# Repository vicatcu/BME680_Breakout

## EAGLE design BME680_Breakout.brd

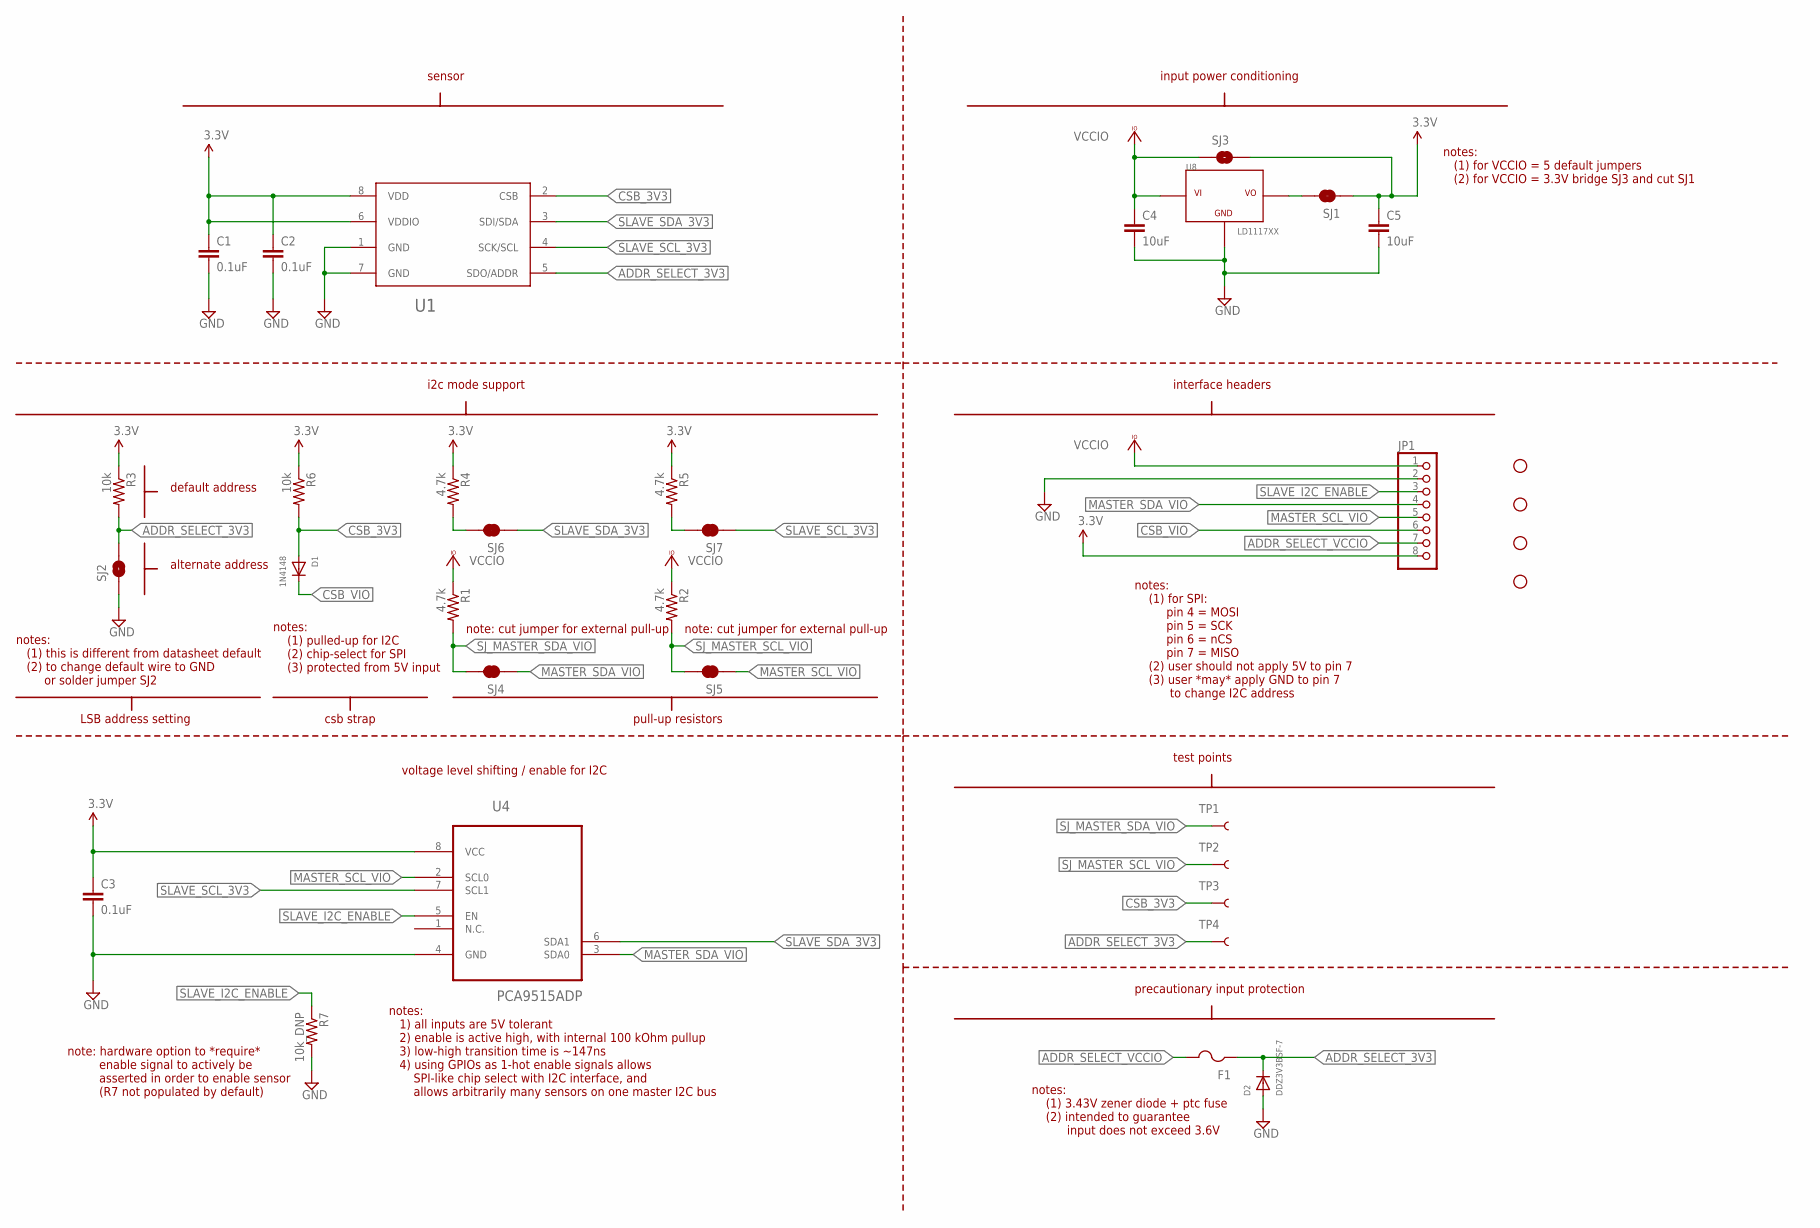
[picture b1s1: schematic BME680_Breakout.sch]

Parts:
C1, C2, C3: 0.1uF; 0805
C4, C5: 10uF; 0805
D1: 1N4148; SOD-323F
D2: DDZ3V3BSF-7; SOD-323F
F1: PTCFUSE-1812; 1812
JP1: PINHD-1X8; 1X08
R1, R2, R4, R5: 4.7k; 0805
R3, R6: 10k; 0805
R7: 10k_DNP; 0805
SJ1, SJ4, SJ5, SJ6, SJ7: JUMPER-PAD-2-NC_BY_TRACE; PAD-JUMPER-2-NC_BY_TRACE_YES_SILK
SJ2: JUMPER-PAD-2-NOYES_SILK; PAD-JUMPER-2-NO_YES_SILK
SJ3: SOLDERJUMPERNC2; SJ_2S-NOTRACE
STANDOFF1, STANDOFF2, STANDOFF3, STANDOFF4: STAND-OFF
TP1, TP2, TP3, TP4: TEST-POINT3X4; PAD.03X.04
U1: BME680
U4: PCA9515ADP; SOT505-1
U8: LD1117XX; DPAK

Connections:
3.3V: C1.1, C2.1, C3.1, C5.1, JP1.8, R3.1, R4.1, R5.1, R6.1, SJ1.1, SJ3.2, U1.6 (VDDIO), U1.8 (VDD), U4.8 (VCC)
ADDR_SELECT_3V3: D2.C, F1.1, R3.2, SJ2.2, TP4.P$1, U1.5 (SDO/ADDR)
ADDR_SELECT_VCCIO: F1.2, JP1.7
CSB_3V3: D1.A, R6.2, TP3.P$1, U1.2 (CSB)
CSB_VIO: D1.C, JP1.6
GND: C1.2, C2.2, C3.2, C4.2, C5.2, D2.A, JP1.2, R7.2, SJ2.1, U1.1 (GND), U1.7 (GND), U4.4 (GND), U8.1 (GND)
MASTER_SCL_VIO: JP1.5, SJ5.1, U4.2 (SCL0)
MASTER_SDA_VIO: JP1.4, SJ4.1, U4.3 (SDA0)
unnamed: SJ1.2, U8.4 (VO)
unnamed: R4.2, SJ6.2
unnamed: R5.2, SJ7.2
SJ_MASTER_SCL_VIO: R2.2, SJ5.2, TP2.P$1
SJ_MASTER_SDA_VIO: R1.2, SJ4.2, TP1.P$1
SLAVE_I2C_ENABLE: JP1.3, R7.1, U4.5 (EN)
SLAVE_SCL_3V3: SJ7.1, U1.4 (SCK/SCL), U4.7 (SCL1)
SLAVE_SDA_3V3: SJ6.1, U1.3 (SDI/SDA), U4.6 (SDA1)
VCCIO: C4.1, JP1.1, R1.1, R2.1, SJ3.1, U8.3 (VI)

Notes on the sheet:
i2c mode support
pull-up resistors
LSB address setting
csb strap
sensor
alternate address
default address
input power conditioning
interface headers
voltage level shifting / enable for I2C
notes: (1) pulled-up for I2C (2) chip-select for SPI (3) protected from 5V input
notes: 1) all inputs are 5V tolerant 2) enable is active high, with internal 100 kOhm pullup 3) low-high transition time is ~147ns 4) using GPIOs as 1-hot enable signals allows SPI-like chip select with I2C interface, and allows arbitrarily many sensors on one master I2C bus
notes: (1) for SPI: pin 4 = MOSI pin 5 = SCK pin 6 = nCS pin 7 = MISO (2) user should not apply 5V to pin 7 (3) user *may* apply GND to pin 7 to change I2C address
notes: (1) this is different from datasheet default (2) to change default wire to GND or solder jumper SJ2
notes: (1) for VCCIO = 5 default jumpers (2) for VCCIO = 3.3V bridge SJ3 and cut SJ1
note: cut jumper for external pull-up
note: hardware option to *require* enable signal to actively be asserted in order to enable sensor (R7 not populated by default)
test points
precautionary input protection
notes: (1) 3.43V zener diode + ptc fuse (2) intended to guarantee input does not exceed 3.6V

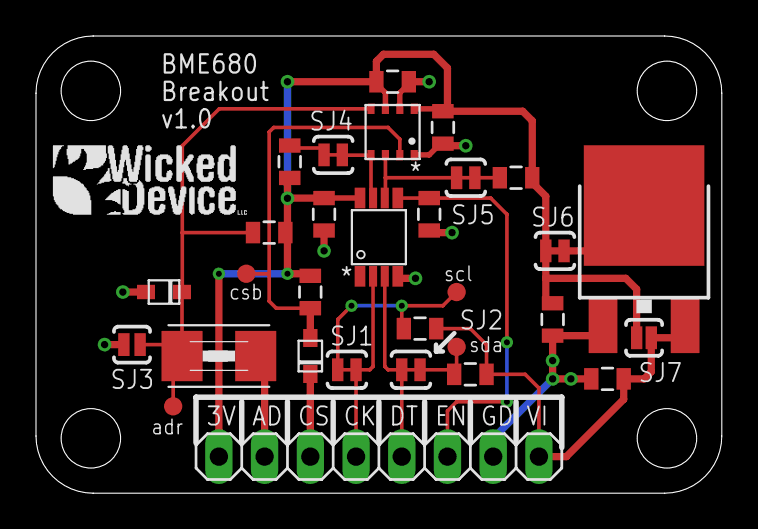
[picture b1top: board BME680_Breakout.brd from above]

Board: 2 copper layers, 38.1 x 25.4 mm, 35 parts (0 on the bottom side), 17 nets.

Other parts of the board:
U$1: WICKEDLOGOTYPE2

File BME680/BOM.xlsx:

LI | Qty | Designators | Manufacturer P/N | CType | Description
1 | 1 | U4 | NXP PCA9515ADP,118 | IC | I2C Multiplexer
2 | 1 | F1 | Bel Fuse Inc 0ZCG0014FF2C | Misc | PTC resettable fuse
3 | 1 | D2 | Diodes Inc. DDZ3V3BSF-7 | Diode | 3.43V Zener Diode
4 | 1 | D1 | Fairchild Semiconductor 1N4148WS | Diode | 1N4148 Diode
5 | 1 | C4, C5 | Kemet C0805C106K8PACTU | Capacitor | 10uF 0805 Capacitor
6 | 1 | U1 | Bosch Sensortec BME680 | Sensor | VOC Sensor
7 | 1 | U8 | STMicroelectronics LD1117DT33CTR | Power | 3.3V Regulator
8 | 3 | C1, C2, C3 | Yageo CC0805ZRY5V9BB104 | Capacitor | 0.1uF 0805 Capacitor
9 | 2 | R3, R6 | Yageo RC0805JR-0710KL | Resistor | 10k 0805 Resistor
10 | 1 | JP1 | 4UCON 00811 | Header | 1x8 Male Header
11 | 4 | R1, R2, R4, R5 | Yageo RC0805JR-074K7L | Resistor | 4.7kOhm 0805 Resistor

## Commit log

2015-12-10 initial schematic commit
2015-12-10 added layout file (not started)
2016-01-09 settled on i2c, renamed some signals, added level shifter logic
2016-01-09 added some support for SPI and wired an 8-pin interface header
2016-01-09 added input power regulator, still need bypass solution, reorganized schematic slightly
2016-01-09 added pull-down hardware option to allow changing default behavior of i2c buffer
2016-01-09 added a few internal test points
2016-01-10 asded zener diode and ptc fuse to address select input
2017-01-29 Initial sketch of driver
2017-01-29 initial routing of PCB
2017-02-06 added silk screen to back side; added to solder jumpers; minor routing changes
2017-03-06 moved component reference designators to tDocu, and labeled solder jumpers and test points on tPlace
2017-04-15 a minimal start at integrating vendor code into an arduino library, at least compiles (though doesn't attept to use any of the vendor code yet)
2017-04-15 hacked common types in vendor files to do something different for arduino
2017-04-15 checking in more wrapping progress, before doing something drastic
2017-04-15 this compiles, but I had to change all their goofy typedefs to use stdint types in all the vendor files to get it to work, which means it will be a little harder to maintain
2017-04-15 fixed obvious bugs; added a bit to the Basic example
2017-04-15 more updates, implemented I2C read function
2017-04-15 implemented i2c burst_read and i2c write
2017-04-15 updated Basic example
2017-04-15 have to call Wire.begin() in setup
2017-06-14 production stuff
2017-07-19 updated based on latest Bosch code
2017-07-20 adding untracked file
2017-07-20 undoing speculative change based on feedback on bosch repo
2017-07-20 minor updates, note baud rate of basic ino changed to 115200
2017-10-22 Replaced i2c read and write function according to succested code in https://github.com/vicatcu/BME680_Breakout/issues/4
2017-10-28 allows compilation for non-avr targets (like esp8266) to work. Works around differences between available signatures in Wire library for some platforms. Addresses #2
2017-10-28 adding esp8266 to library.properties architectures
2017-11-21 updated vendor library code to v3.5.5
2018-03-22 updated to latest Bosch driver code, example compiles without error

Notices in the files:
parts and their libraries:
SparkFun-Passives: Licensing: Creative Commons ShareAlike 4.0 International - https://creativecommons.org/licenses/by-sa/4.0
